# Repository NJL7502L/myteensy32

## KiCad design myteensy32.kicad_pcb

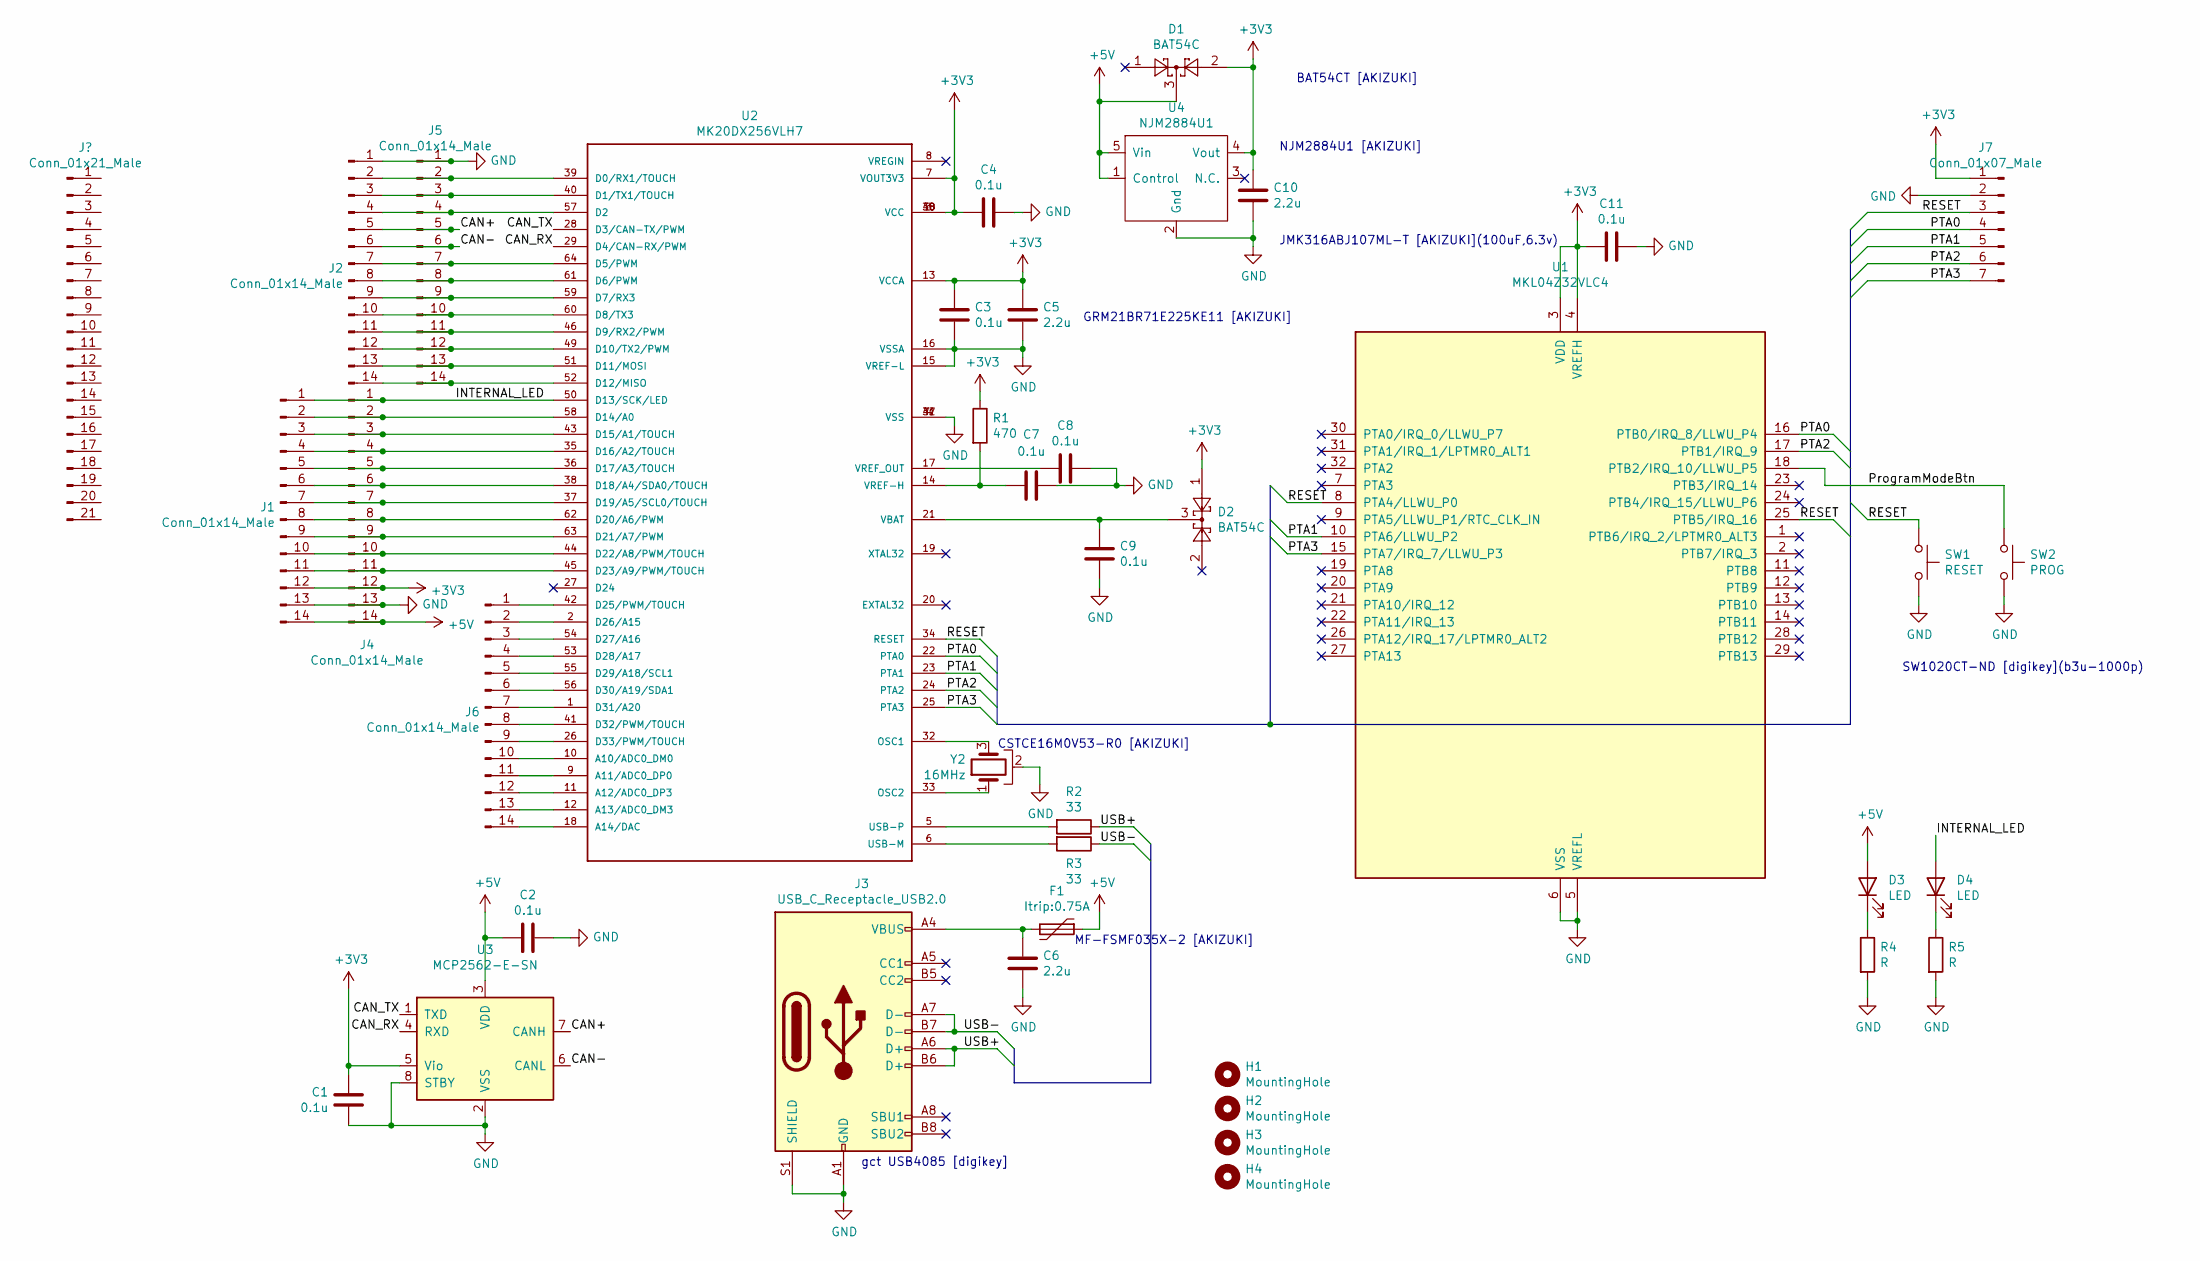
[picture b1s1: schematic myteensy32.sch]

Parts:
C1, C2, C3, C4, C7, C8, C9, C11: 0.1u; C_0603_1608Metric
C5, C6, C10: 2.2u; C_0805_2012Metric
D1, D2: BAT54C; SOT-23
D3, D4: LED; LED_1608_point
F1: Itrip:0.75A; Fuse_0603_1608Metric
H1, H2, H3, H4: MountingHole; Hole_3.2mm_NPTH
J1, J2, J4, J5, J6: Conn_01x14_Male; PinHeader_1x14_P2.54mm_Vertical
J3: USB_C_Receptacle_USB2.0; USB_C_Receptacle_GCT_USB4085
J7: Conn_01x07_Male; PinSocket_1x07_P2.54mm_Vertical
R1: 470; R_0603_1608Metric
R2, R3: 33; R_0603_1608Metric
R4, R5: R; R_0603_1608Metric
SW1: RESET; SW_SPST_B3U-1000P
SW2: PROG; SW_SPST_B3U-1000P
U1: MKL04Z32VLC4; LQFP-32_7x7mm_P0.8mm
U2: MK20DX256VLH7; QFP50P1200X1200X160-64N
U3: MCP2562-E-SN; SOIC-8_3.9x4.9mm_P1.27mm
U4: NJM2884U1; SOT-89-5
Y2: 16MHz; CSTCE16M0V53-R0

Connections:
+3V3: C1.2, C3.2, C4.2, C5.1, C10.1, C11.2, D1.2, D2.1, J1.12, J4.12, J7.1, R1.1, U1.3 (VDD), U1.4 (VREFH), U2.3 (VCC), U2.7 (VOUT3V3), U2.13 (VCCA), U2.30 (VCC), U2.48 (VCC), U3.5 (Vio), U4.4 (Vout)
+5V: C2.2, D1.3, D3.2 (A), F1.1, J1.14, J4.14, U3.3 (VDD), U4.1 (Control), U4.5 (Vin)
/CAN+: J2.5, J5.5, U3.7 (CANH)
/CAN-: J2.6, J5.6, U3.6 (CANL)
/CAN_RX: U2.29 (D4/CAN-RX/PWM), U3.4 (RXD)
/CAN_TX: U2.28 (D3/CAN-TX/PWM), U3.1 (TXD)
/INTERNAL_LED: D4.2 (A), J1.1, J4.1, U2.50 (D13/SCK/LED)
/PTA0: J7.4, U1.16 (PTB0/IRQ_8/LLWU_P4), U2.22 (PTA0)
/PTA1: J7.5, U1.10 (PTA6/LLWU_P2), U2.23 (PTA1)
/PTA2: J7.6, U1.17 (PTB1/IRQ_9), U2.24 (PTA2)
/PTA3: J7.7, U1.15 (PTA7/IRQ_7/LLWU_P3), U2.25 (PTA3)
/ProgramModeBtn: SW2.1, U1.18 (PTB2/IRQ_10/LLWU_P5)
/RESET: J7.3, SW1.1, U1.8 (PTA4/LLWU_P0), U1.25 (PTB5/IRQ_16), U2.34 (RESET)
/USB+: J3.A6 (D+), J3.B6 (D+), R2.1
/USB-: J3.A7 (D-), J3.B7 (D-), R3.1
GND: C1.1, C2.1, C3.1, C4.1, C5.2, C6.1, C7.1, C8.1, C9.2, C10.2, C11.1, J1.13, J2.1, J3.A1 (GND), J3.A12 (GND), J3.B1 (GND), J3.B12 (GND), J3.S1 (SHIELD), J4.13, J5.1, J7.2, R4.2, R5.2, SW1.2, SW2.2, U1.5 (VREFL), U1.6 (VSS), U2.4 (VSS), U2.15 (VREF-L), U2.16 (VSSA), U2.31 (VSS), U2.47 (VSS), U3.2 (VSS), U3.8 (STBY), U4.2 (Gnd), Y2.2
unnamed: C6.2, F1.2, J3.A4 (VBUS), J3.A9 (VBUS), J3.B4 (VBUS), J3.B9 (VBUS)
unnamed: C7.2, R1.2, U2.14 (VREF-H)
unnamed: C8.2, U2.17 (VREF_OUT)
unnamed: C9.1, D2.3, U2.21 (VBAT)
unnamed: D3.1 (K), R4.1
unnamed: D4.1 (K), R5.1
unnamed: J1.2, J4.2, U2.58 (D14/A0)
unnamed: J1.3, J4.3, U2.43 (D15/A1/TOUCH)
unnamed: J1.4, J4.4, U2.35 (D16/A2/TOUCH)
unnamed: J1.5, J4.5, U2.36 (D17/A3/TOUCH)
unnamed: J1.6, J4.6, U2.38 (D18/A4/SDA0/TOUCH)
unnamed: J1.7, J4.7, U2.37 (D19/A5/SCL0/TOUCH)
unnamed: J1.8, J4.8, U2.62 (D20/A6/PWM)
unnamed: J1.9, J4.9, U2.63 (D21/A7/PWM)
unnamed: J1.10, J4.10, U2.44 (D22/A8/PWM/TOUCH)
unnamed: J1.11, J4.11, U2.45 (D23/A9/PWM/TOUCH)
unnamed: J2.2, J5.2, U2.39 (D0/RX1/TOUCH)
unnamed: J2.3, J5.3, U2.40 (D1/TX1/TOUCH)
unnamed: J2.4, J5.4, U2.57 (D2)
unnamed: J2.7, J5.7, U2.64 (D5/PWM)
unnamed: J2.8, J5.8, U2.61 (D6/PWM)
unnamed: J2.9, J5.9, U2.59 (D7/RX3)
unnamed: J2.10, J5.10, U2.60 (D8/TX3)
unnamed: J2.11, J5.11, U2.46 (D9/RX2/PWM)
unnamed: J2.12, J5.12, U2.49 (D10/TX2/PWM)
unnamed: J2.13, J5.13, U2.51 (D11/MOSI)
unnamed: J2.14, J5.14, U2.52 (D12/MISO)
unnamed: J6.1, U2.42 (D25/PWM/TOUCH)
unnamed: J6.2, U2.2 (D26/A15)
unnamed: J6.3, U2.54 (D27/A16)
unnamed: J6.4, U2.53 (D28/A17)
unnamed: J6.5, U2.55 (D29/A18/SCL1)
unnamed: J6.6, U2.56 (D30/A19/SDA1)
unnamed: J6.7, U2.1 (D31/A20)
unnamed: J6.8, U2.41 (D32/PWM/TOUCH)
unnamed: J6.9, U2.26 (D33/PWM/TOUCH)
unnamed: J6.10, U2.10 (A10/ADC0_DM0)
unnamed: J6.11, U2.9 (A11/ADC0_DP0)
unnamed: J6.12, U2.11 (A12/ADC0_DP3)
unnamed: J6.13, U2.12 (A13/ADC0_DM3)
unnamed: J6.14, U2.18 (A14/DAC)
unnamed: R2.2, U2.5 (USB-P)
unnamed: R3.2, U2.6 (USB-M)
unnamed: U2.32 (OSC1), Y2.3
unnamed: U2.33 (OSC2), Y2.1

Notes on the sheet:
CSTCE16M0V53-R0 [AKIZUKI]
gct USB4085 [digikey]
MF-FSMF035X-2 [AKIZUKI]
NJM2884U1 [AKIZUKI]
BAT54CT [AKIZUKI]
SW1020CT-ND [digikey](b3u-1000p)
GRM21BR71E225KE11 [AKIZUKI]
JMK316ABJ107ML-T [AKIZUKI](100uF,6.3v)

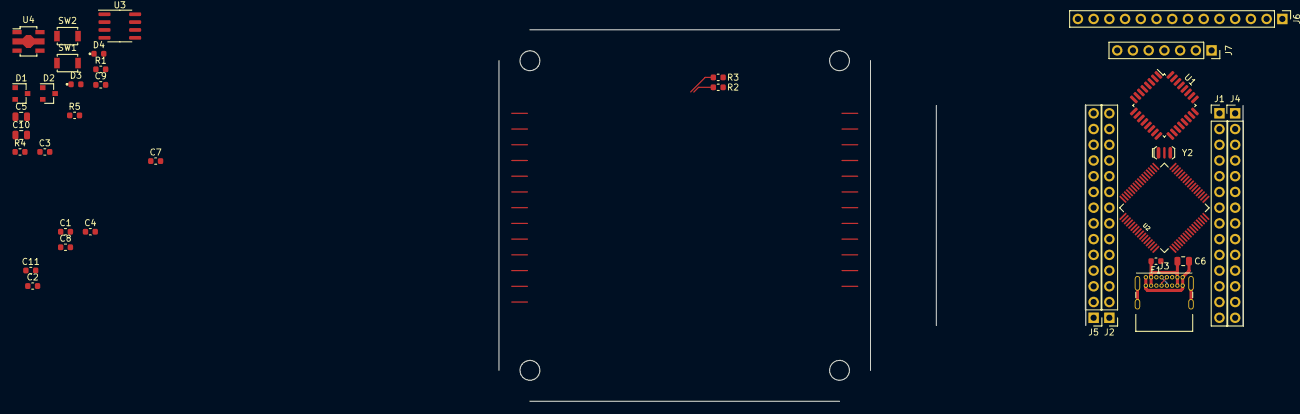
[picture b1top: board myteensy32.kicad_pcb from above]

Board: 2 copper layers, 39 parts (0 on the bottom side), 61 nets.

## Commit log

2020-09-01 すべてを削除してネットリストの再読み込み
2020-09-02 Connectorを追加
2020-09-02 wideな感じで配線してみる
